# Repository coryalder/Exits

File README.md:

# HEAR

### ⚠️ THIS MODULE WORKS, BUT HASN'T BEEN TESTED THUROUGHLY YET ⚠️

HEAR is a DIY 8hp eurorack module designed to be the output stage of your patches. It has a 4 channel mixer with individual pan and level controls, and line and headphone outputs.

The project was derived from the [Exits](https://github.com/ramphands/Exits) module. Exits was a combination of the lines mixer project [Nearness](https://github.com/sarnesjo/nearness) and the [Forestcaver headphone amp](https://github.com/forestcaver/Analog-Voice/tree/master/AJH_Headphone_Amp). For HEAR The patch-based stereo panning of Exits and nearness was changed out for individual pan and level controls for 4 tracks, and the Forestcaver headphone amp (based on the NJM4556AV-TE1 opamp) was changed out for a headphone amp loosely based on Chu Moy's famous ["CMoy" design](https://web.archive.org/web/20021223020724/http://headwize2.powerpill.org/projects/showproj.php?file=cmoy2_prj.htm) - in this case using the RC4580 instead of the OPA134 for availability and experimentation reasons. The module was expanded from 4hp to 8hp to accomodate the extra knobs. I also switched from 1/4" jacks for the two outputs - to 1/8" jacks for everything. The extra space on the widened input board, along with removing the two tall 1/4" jacks, allowed me to flatten the module from two PCBs to just one.

If you'd like to explore the pan + mix section, circuitjs simulation files are in the [simulations](simulations) directory.

The four mixer channels are DC coupled, so you can use this module to mix CV. The headphone output is not DC coupled, so only the line output will output DC offsets. At maximum volume the headphone output is about 1/10 the input level. J5 and J6 are jumpers - no pins bridged means the mixer has a gain of about 1x. Bridging pins 1 and 2 on both jumpers will set the mixer sections gain to 2/3x in case you're mixing hot signals and want to tone things down a bit. To add gain, you could bridge pins 1+2 and then desolder R17 and R20. That'll set the gain to just shy of 2x.

The following sources were used either directly or as learning material to construct the panning and mixing section:

- [Audio Signal Mixing](https://sound-au.com/articles/audio-mixing.htm) By Rod Elliott - a fantastic explainer of mixing circuits
- Erica Synths DIY eurorack [Output and Mixer](https://github.com/erica-synths/diy-eurorack) modules
- [Befaco Hexmix](http://www.befaco.org/hexmix/)

## Schematic and PCBs

The [kicad](kicad) directory contains the schematic and PCB layout as a KiCad 6 project.

Gerber files are generated by [Bouni's Kicad JLCPCB tools](https://github.com/Bouni/kicad-jlcpcb-tools) - latest files are located in [kicad/jlcpcb](kicad/jlcpcb). These are still untested. This page will be updated when they have been tested and are KNOWN working.

## Panel

The panel for HEAR has been generated by [Crows Eurorack Laser Panels](https://crowselectromusic.com/tools/laser/panels/). The panel definition file is located in the [panel](panel) directory, ypu can use that to generate an SVG or DXF file.

## Revisions and notes 

- Started with this commit of [Exits](https://github.com/ramphands/Exits/tree/e56ce6f3a76ff6dc0b776ba10d0bfae7fea7ace0).
- HEAR's first "complete" post-Exits scheamtic, using passive mixing can be found in the git history [here](https://github.com/crowselectromusic/HEAR/blob/65a9d2693df2f5ae9116ffd591f22e5cf609d3db/exits%20schematic.april12th.pdf). After that I switched to current based mixing, per Rod Elliott's article
- HEAR's first "complete" + "current-based" schematic is [here](https://github.com/crowselectromusic/HEAR/tree/e56ce6f3a76ff6dc0b776ba10d0bfae7fea7ace0).
- Fixed routing so left is on the left and right is on the right, [schematic](https://github.com/crowselectromusic/HEAR/blob/033efc4fa74acb90b556fa5d66f9de59aaeca7dc/exits%20schematic.pdf).

## License

[CC BY-SA 4.0](http://creativecommons.org/licenses/by-sa/4.0/)

To summarize the license linked above - you are free to:

* Share — copy and redistribute the material in any medium or format
* Adapt — remix, transform, and build upon the material
for any purpose, even commercially. 

As long as you abide by the terms of the license which requires:

* Attribution — You must give appropriate credit, provide a link to the license, and indicate if changes were made. You may do so in any reasonable manner, but not in any way that suggests the licensor endorses you or your use.

* ShareAlike — If you remix, transform, or build upon the material, you must distribute your contributions under the same license as the original.

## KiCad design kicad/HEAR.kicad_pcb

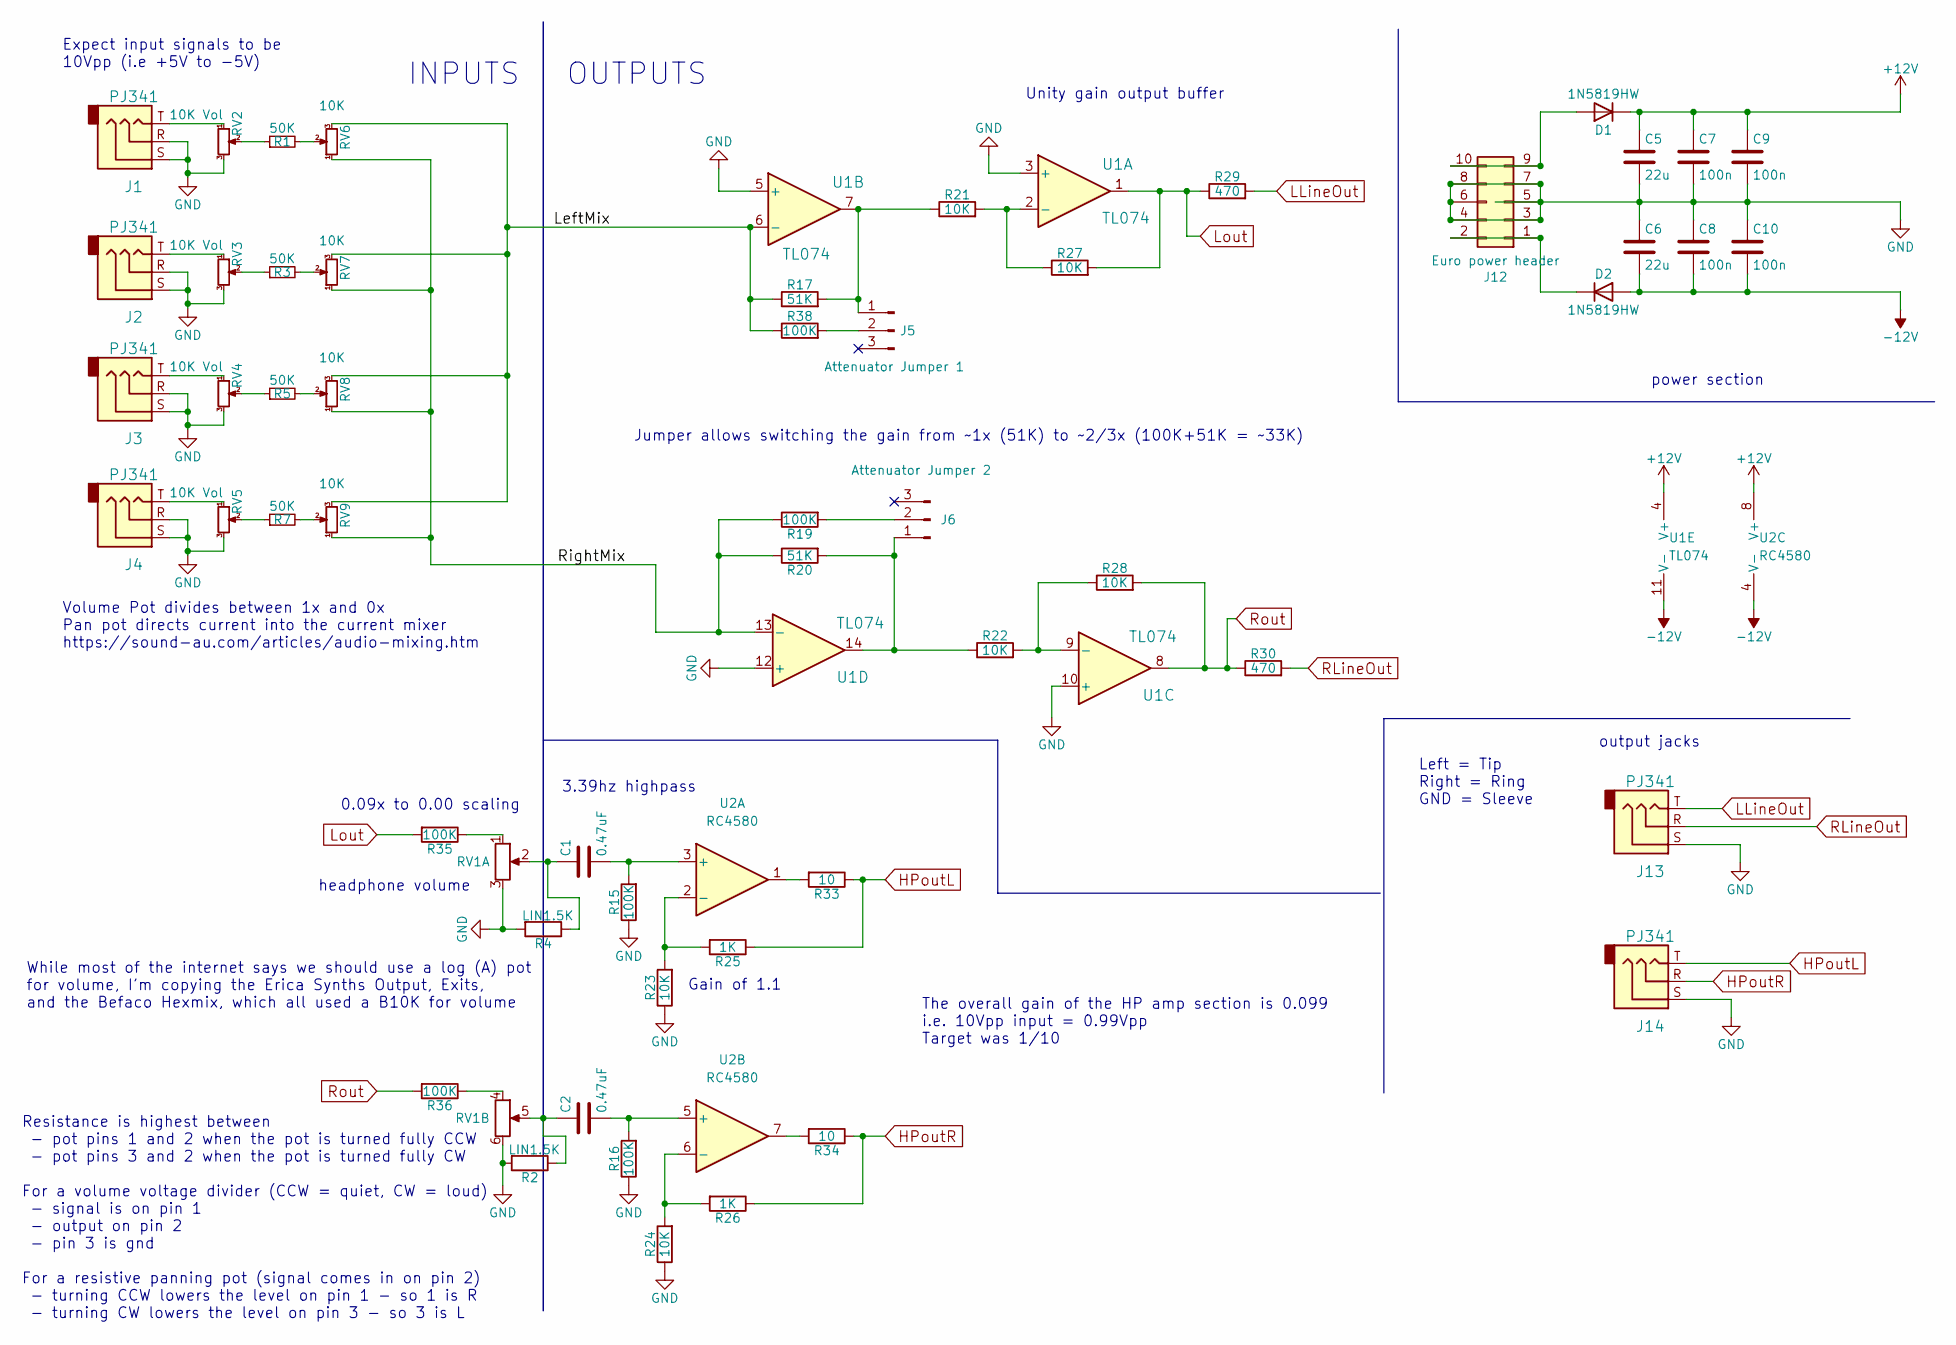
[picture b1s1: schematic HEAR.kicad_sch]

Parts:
C1, C2: 0.47uF; C_1206_3216Metric_Pad1.33x1.80mm_HandSolder; LCSC C1868
C5, C6: 22u; C_1206_3216Metric_Pad1.33x1.80mm_HandSolder; LCSC C12891
C7, C8, C9, C10: 100n; C_0603_1608Metric_Pad1.08x0.95mm_HandSolder; LCSC C14663
D1, D2: 1N5819HW; D_SOD-323_HandSoldering; LCSC C191023
J1, J2, J3, J4, J13, J14: PJ341; PJ341_3.5mm_headphone
J5: Attenuator Jumper 1; PinHeader_1x03_P2.54mm_Vertical
J6: Attenuator Jumper 2; PinHeader_1x03_P2.54mm_Vertical
J12: Euro power header; IDC-Header_2x05_P2.54mm_Vertical
R1, R3, R5, R7: 50K; R_0603_1608Metric_Pad0.98x0.95mm_HandSolder; LCSC C23196
R2, R4: LIN1.5K; R_Axial_DIN0207_L6.3mm_D2.5mm_P2.54mm_Vertical
R15, R16, R35, R36: 100K; R_0805_2012Metric_Pad1.20x1.40mm_HandSolder; LCSC C149504
R17, R20: 51K; R_0603_1608Metric_Pad0.98x0.95mm_HandSolder; LCSC C23196
R19, R38: 100K; R_0603_1608Metric_Pad0.98x0.95mm_HandSolder; LCSC C25803
R21, R22, R23, R24, R27, R28: 10K; R_0603_1608Metric_Pad0.98x0.95mm_HandSolder; LCSC C25804
R25, R26: 1K; R_0603_1608Metric_Pad0.98x0.95mm_HandSolder; LCSC C21190
R29, R30: 470; R_0603_1608Metric_Pad0.98x0.95mm_HandSolder; LCSC C23179
R33, R34: 10; R_1206_3216Metric_Pad1.30x1.75mm_HandSolder; LCSC C17903
RV1: B10K; RV1666G-F
RV2, RV3, RV4, RV5: 10K Vol; Potentiometer_Rotary_9mm_Vertical_Single
RV6, RV7, RV8, RV9: 10K; Potentiometer_Rotary_9mm_Vertical_Single
U1: TL074; SOIC-14_3.9x8.7mm_P1.27mm; LCSC C12594
U2: RC4580; SOIC-8_3.9x4.9mm_P1.27mm; LCSC C80100

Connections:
+12V: C5.1, C7.1, C9.1, D1.1 (K), U1.4 (V+), U2.8 (V+)
-12V: C6.2, C8.2, C10.2, D2.2 (A), U1.11 (V-), U2.4 (V-)
/LeftMix: R17.1, R38.1, RV6.3, RV7.3, RV8.3, RV9.3, U1.6 (-)
/RightMix: R19.1, R20.1, RV6.1, RV7.1, RV8.1, RV9.1, U1.13 (-)
GND: C5.2, C6.1, C7.2, C8.1, C9.2, C10.1, J1.R, J1.S, J2.R, J2.S, J3.R, J3.S, J4.R, J4.S, J12.3, J12.4, J12.5, J12.6, J12.7, J12.8, J13.S, J14.S, R2.2, R4.2, R15.1, R16.1, R23.1, R24.1, RV1.3, RV1.6, RV2.3, RV3.3, RV4.3, RV5.3, U1.3 (+), U1.5 (+), U1.10 (+), U1.12 (+)
HPoutL: J14.T, R25.1, R33.1
HPoutR: J14.R, R26.1, R34.1
LLineOut: J13.T, R29.2
Lout: R27.2, R29.1, R35.2, U1.1
unnamed: C1.1, R4.1, RV1.2
unnamed: C1.2, R15.2, U2.3 (+)
unnamed: C2.1, R2.1, RV1.5
unnamed: C2.2, R16.2, U2.5 (+)
unnamed: D1.2 (A), J12.9, J12.10
unnamed: D2.1 (K), J12.1, J12.2
unnamed: J1.T, RV2.1
unnamed: J2.T, RV3.1
unnamed: J3.T, RV4.1
unnamed: J4.T, RV5.1
unnamed: J5.1, R17.2, R21.1, U1.7
unnamed: J5.2, R38.2
unnamed: J6.1, R20.2, R22.1, U1.14
unnamed: J6.2, R19.2
unnamed: R1.1, RV2.2
unnamed: R1.2, RV6.2
unnamed: R3.1, RV3.2
unnamed: R3.2, RV7.2
unnamed: R5.1, RV4.2
unnamed: R5.2, RV8.2
unnamed: R7.1, RV5.2
unnamed: R7.2, RV9.2
unnamed: R21.2, R27.1, U1.2 (-)
unnamed: R22.2, R28.1, U1.9 (-)
unnamed: R23.2, R25.2, U2.2 (-)
unnamed: R24.2, R26.2, U2.6 (-)
unnamed: R33.2, U2.1
unnamed: R34.2, U2.7
unnamed: R35.1, RV1.1
unnamed: R36.1, RV1.4
RLineOut: J13.R, R30.2
Rout: R28.2, R30.1, R36.2, U1.8

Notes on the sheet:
The overall gain of the HP amp section is 0.099 i.e. 10Vpp input = 0.99Vpp Target was 1/10
headphone volume
3.39hz highpass
INPUTS
Volume Pot divides between 1x and 0x Pan pot directs current into the current mixer https://sound-au.com/articles/audio-mixing.htm
Left = Tip Right = Ring GND = Sleeve
Unity gain output buffer
0.09x to 0.00 scaling
Gain of 1.1
While most of the internet says we should use a log (A) pot for volume, I'm copying the Erica Synths Output, Exits, and the Befaco Hexmix, which all used a B10K for volume
OUTPUTS
Jumper allows switching the gain from ~1x (51K) to ~2/3x (100K+51K = ~33K)
output jacks
Expect input signals to be 10Vpp (i.e +5V to -5V)
power section
Resistance is highest between - pot pins 1 and 2 when the pot is turned fully CCW - pot pins 3 and 2 when the pot is turned fully CW For a volume voltage divider (CCW = quiet, CW = loud) - signal is on pin 1 - output on pin 2 - pin 3 is gnd For a resistive panning pot (signal comes in on pin 2) - t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

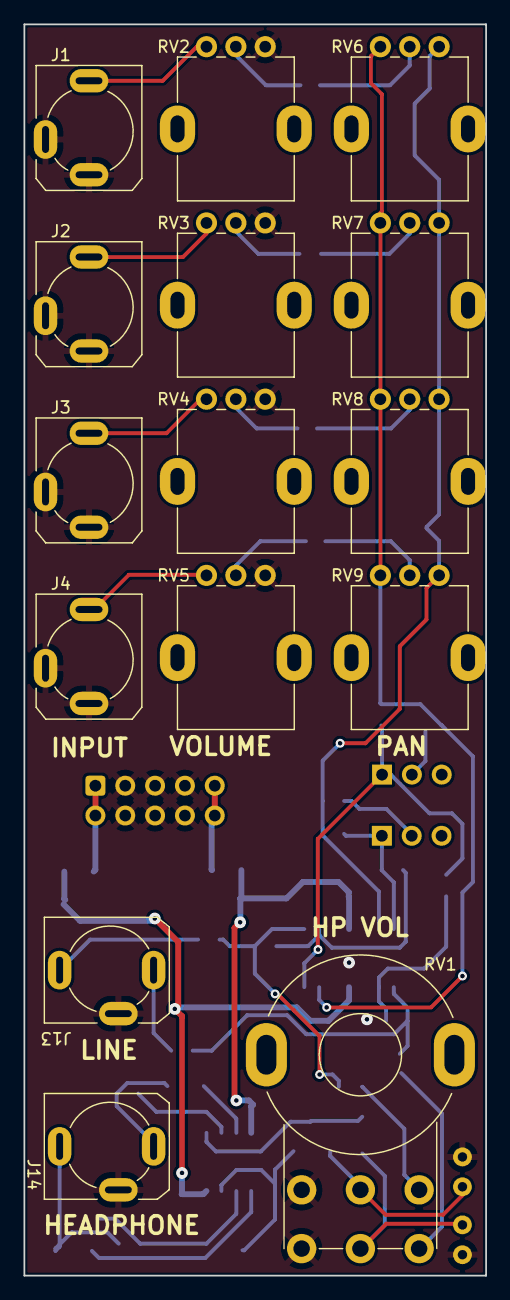
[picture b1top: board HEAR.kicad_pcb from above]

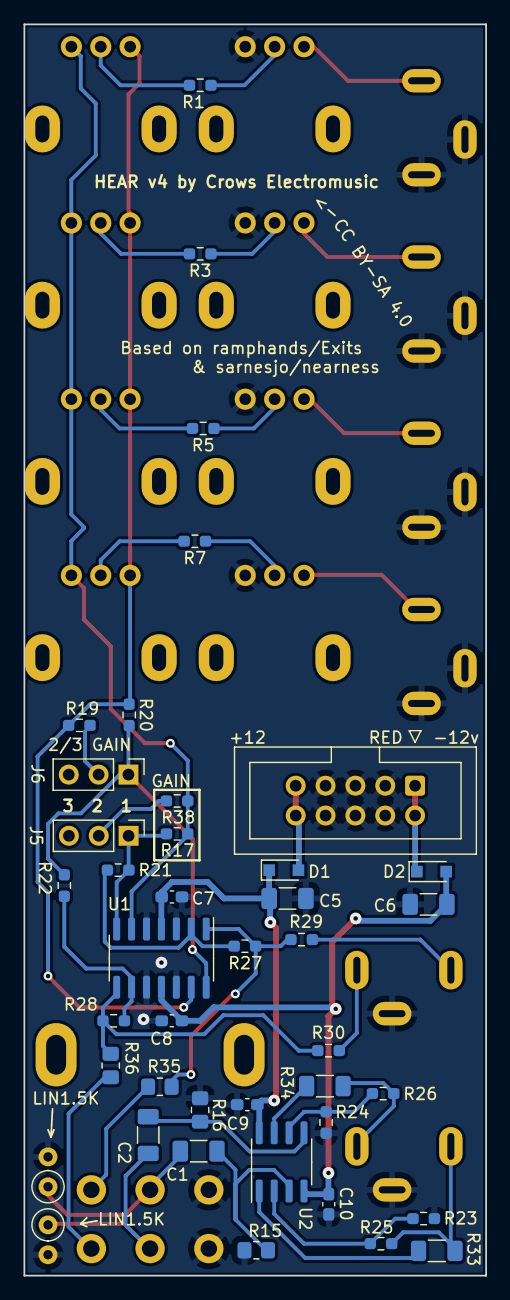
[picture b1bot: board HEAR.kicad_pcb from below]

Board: 2 copper layers, 39.3 x 106.5 mm, 56 parts (41 on the bottom side), 41 nets.

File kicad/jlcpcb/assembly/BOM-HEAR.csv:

Comment,Designator,Footprint,LCSC
TL074,U1,SOIC-14_3.9x8.7mm_P1.27mm,C12594
22u,"C5,C6",C_1206_3216Metric_Pad1.33x1.80mm_HandSolder,C12891
100n,"C10,C7,C8,C9",C_0603_1608Metric_Pad1.08x0.95mm_HandSolder,C14663
100K,"R15,R16,R35,R36",R_0805_2012Metric_Pad1.20x1.40mm_HandSolder,C149504
10,"R33,R34",R_1206_3216Metric_Pad1.30x1.75mm_HandSolder,C17903
0.47uF,"C1,C2",C_1206_3216Metric_Pad1.33x1.80mm_HandSolder,C1868
1N5819HW,"D1,D2",D_SOD-323_HandSoldering,C191023
1K,"R25,R26",R_0603_1608Metric_Pad0.98x0.95mm_HandSolder,C21190
470,"R29,R30",R_0603_1608Metric_Pad0.98x0.95mm_HandSolder,C23179
50K,"R1,R17,R20,R3,R5,R7",R_0603_1608Metric_Pad0.98x0.95mm_HandSolder,C23196
100K,"R19,R38",R_0603_1608Metric_Pad0.98x0.95mm_HandSolder,C25803
10K,"R21,R22,R23,R24,R27,R28",R_0603_1608Metric_Pad0.98x0.95mm_HandSolder,C25804
RC4580,U2,SOIC-8_3.9x4.9mm_P1.27mm,C80100
PJ341,J2,PJ341_3.5mm_headphone,
10K,RV9,Potentiometer_Rotary_9mm_Vertical_Single,
PJ341,J1,PJ341_3.5mm_headphone,
PJ341,J3,PJ341_3.5mm_headphone,
10K Vol,RV2,Potentiometer_Rotary_9mm_Vertical_Single,
10K,RV7,Potentiometer_Rotary_9mm_Vertical_Single,
10K,RV8,Potentiometer_Rotary_9mm_Vertical_Single,
B10K,RV1,RV1666G-F,
10K Vol,RV4,Potentiometer_Rotary_9mm_Vertical_Single,
PJ341,J13,PJ341_3.5mm_headphone,
10K Vol,RV3,Potentiometer_Rotary_9mm_Vertical_Single,
10K Vol,RV5,Potentiometer_Rotary_9mm_Vertical_Single,
10K,RV6,Potentiometer_Rotary_9mm_Vertical_Single,
PJ341,J4,PJ341_3.5mm_headphone,
PJ341,J14,PJ341_3.5mm_headphone,
Euro power header,J12,IDC-Header_2x05_P2.54mm_Vertical,
Attenuator Jumper 1,J5,PinHeader_1x03_P2.54mm_Vertical,
LIN1.5K,R2,R_Axial_DIN0207_L6.3mm_D2.5mm_P2.54mm_Vertical,
Attenuator Jumper 2,J6,PinHeader_1x03_P2.54mm_Vertical,
LIN1.5K,R4,R_Axial_DIN0207_L6.3mm_D2.5mm_P2.54mm_Vertical,

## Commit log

2022-04-20 Moved todos out of readme, formatting changes
2022-04-20 note about pot taper
2022-05-09 removed unused board files
2022-05-09 switch to PJ358s for stereo output
2022-06-02 switch to PJ341s, add linearizing Rs
2022-06-02 rename to HEAR
2022-06-02 added JLCPCB part numbers
2022-06-02 updated diode footprint for new jlcpart
2022-06-02 gerbers for v01
2022-06-02 update ibom
2022-06-03 re-route for better symmetry
2022-06-03 heal broken footprint lib path
2022-06-03 fixed silkscreen errs in footprint
2022-06-04 footprints submodule
2022-06-04 3d model for pj341
2022-06-04 writable url for git submodule
2022-06-04 switch to jlcpcb plugin to generate output
2022-06-04 idk some small change
2022-06-04 v02 uploaded
2022-06-04 Updated submodule
2022-06-04 updated library, new footprint names
2022-06-04 reloaded footprints
2022-06-04 update readme, start panel file
2022-06-08 v3 gerbers (had to swap out a cap, part no longer available
2022-06-21 add image
2022-06-21 add 3d renderings, closes issue #5
2023-03-08 Update panel definition file
2023-03-08 Fix pj341 footprint, tidy up spacing of things
2023-03-16 tweak stereo pot footprint
2024-01-17 updated panel file to match the pcb
